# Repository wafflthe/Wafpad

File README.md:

# Wafpad
A lil macropad with some screens and stuff

Green area at the bottom is for the .91" OLED display I just couldent find a 3d model for it

# Inspiration
Mainly inspired by the stream deck neo but without the angled case (Will be added to CAD in the future)

# Case CAD
Top and bottom CAD files for case 

Designed in onshape

# PCB and Schematic
I used Kicad to design both the PCB and Schematic

I used a 2x8 matrix to get all of the keys to fit as I diddnt have enough gpio ports

# BOM
Everything to make a Wafpad!
- 1x XIAO RP2040 (with headers)
- 1x EC11 Rotary Encoder
- 1x 0.91" OLED Display
- 8x Cherry MX Switches
- 8x Blank DSA Keycaps
- 8x Diode (THT)
- 8x SK6812 Mini LEDs

Case

- 4x M3x16mm screws
- 4x M3x5mx4mm heatset inserts
- 1x Wafpad case v1.step
- 1x Wafpad top v1.step

# Firmware
Currently havent made it because im not sure how to without having the pcb to use kmk, so I currently have the example doc from the hackpad tutorial but I will update this after I make and program it

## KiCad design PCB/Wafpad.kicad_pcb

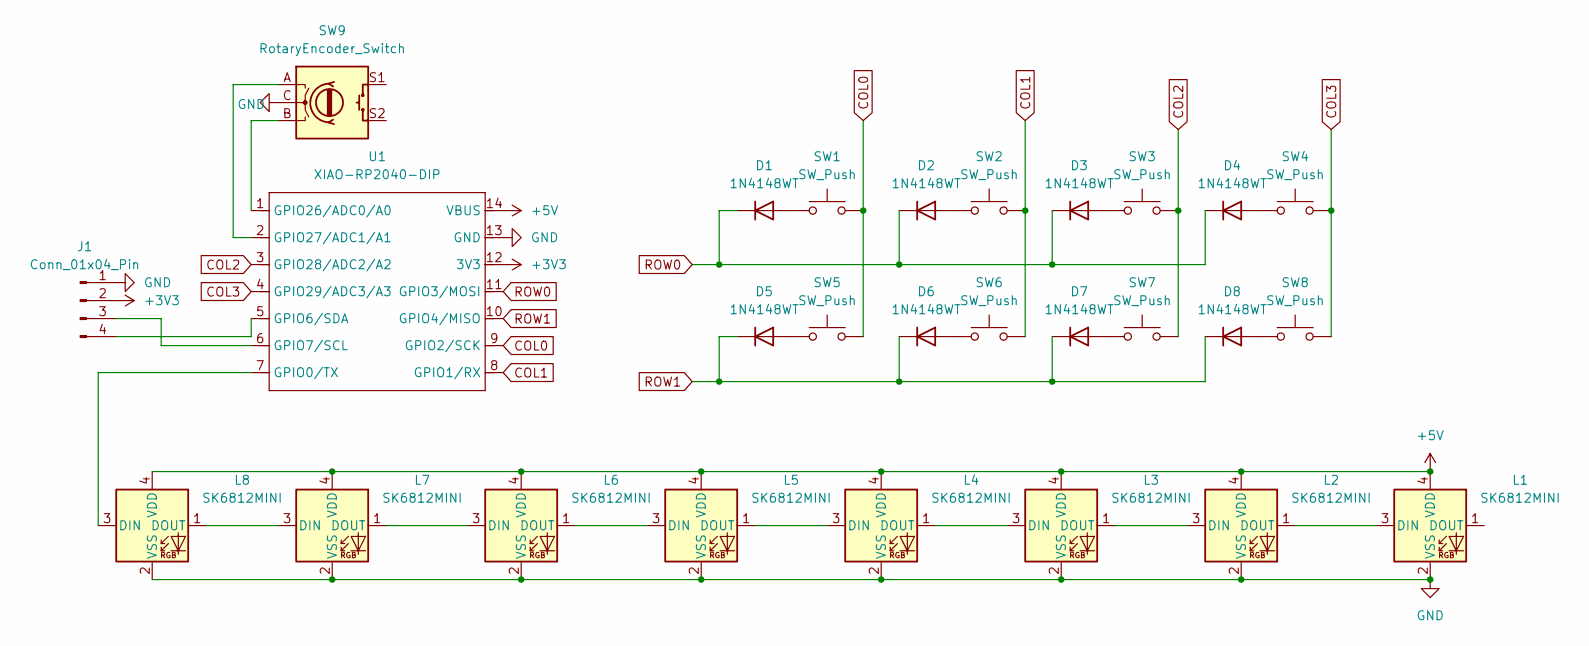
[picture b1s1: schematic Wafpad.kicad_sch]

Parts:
D1, D2, D3, D4, D5, D6, D7, D8: 1N4148WT; D_DO-35_SOD27_P7.62mm_Horizontal
J1: Conn_01x04_Pin; SSD1306-0.91-OLED-4pin-128x32
L1, L2, L3, L4, L5, L6, L7, L8: SK6812MINI; SK6812MINI-E_fixed
SW1, SW2, SW3, SW4, SW5, SW6, SW7, SW8: SW_Push; SW_Cherry_MX_1.00u_PCB
SW9: RotaryEncoder_Switch; RotaryEncoder_Alps_EC11E-Switch_Vertical_H20mm
U1: XIAO-RP2040-DIP

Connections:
+3V3: J1.2, U1.12 (3V3)
+5V: L1.4 (VDD), L2.4 (VDD), L3.4 (VDD), L4.4 (VDD), L5.4 (VDD), L6.4 (VDD), L7.4 (VDD), L8.4 (VDD), U1.14 (VBUS)
COL0: SW1.2, SW5.2, U1.9 (GPIO2/SCK)
COL1: SW2.2, SW6.2, U1.8 (GPIO1/RX)
COL2: SW3.2, SW7.2, U1.3 (GPIO28/ADC2/A2)
COL3: SW4.2, SW8.2, U1.4 (GPIO29/ADC3/A3)
GND: J1.1, L1.2 (VSS), L2.2 (VSS), L3.2 (VSS), L4.2 (VSS), L5.2 (VSS), L6.2 (VSS), L7.2 (VSS), L8.2 (VSS), SW9.C, U1.13 (GND)
unnamed: D1.2 (A), SW1.1
unnamed: D2.2 (A), SW2.1
unnamed: D3.2 (A), SW3.1
unnamed: D4.2 (A), SW4.1
unnamed: D5.2 (A), SW5.1
unnamed: D6.2 (A), SW6.1
unnamed: D7.2 (A), SW7.1
unnamed: D8.2 (A), SW8.1
unnamed: J1.3, U1.6 (GPIO7/SCL)
unnamed: J1.4, U1.5 (GPIO6/SDA)
unnamed: L1.3 (DIN), L2.1 (DOUT)
unnamed: L2.3 (DIN), L3.1 (DOUT)
unnamed: L3.3 (DIN), L4.1 (DOUT)
unnamed: L4.3 (DIN), L5.1 (DOUT)
unnamed: L5.3 (DIN), L6.1 (DOUT)
unnamed: L6.3 (DIN), L7.1 (DOUT)
unnamed: L7.3 (DIN), L8.1 (DOUT)
unnamed: L8.3 (DIN), U1.7 (GPIO0/TX)
unnamed: SW9.B, U1.1 (GPIO26/ADC0/A0)
unnamed: SW9.A, U1.2 (GPIO27/ADC1/A1)
ROW0: D1.1 (K), D2.1 (K), D3.1 (K), D4.1 (K), U1.11 (GPIO3/MOSI)
ROW1: D5.1 (K), D6.1 (K), D7.1 (K), D8.1 (K), U1.10 (GPIO4/MISO)

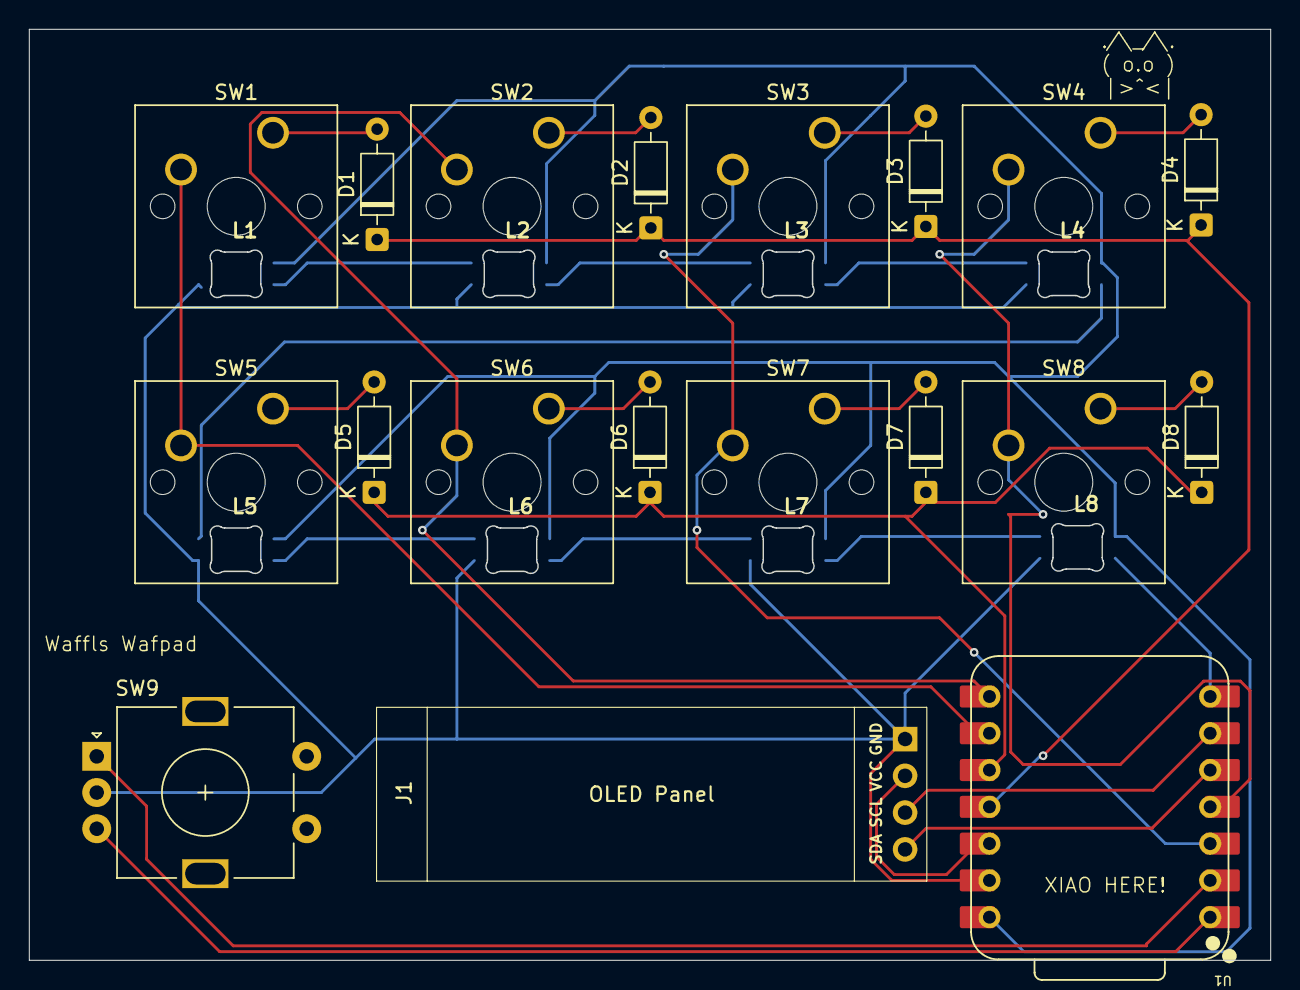
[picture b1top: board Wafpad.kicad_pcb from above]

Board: 2 copper layers, 85.7 x 64.2 mm, 27 parts (0 on the bottom side), 29 nets.

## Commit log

2025-12-15 Add README
2025-12-18 small update
2025-12-18 added bom.csv
2025-12-18 updated BOM
2025-12-18 added BOM
2025-12-18 photo update
2025-12-18 tiny
2025-12-18 updatedBOM
2025-12-18 update BOM
